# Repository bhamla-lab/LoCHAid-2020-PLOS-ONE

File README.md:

# LoCHAid
Repository for Addressing Age Related Hearing Loss through engineering accessible and affordable hearing technology
Data from ANSI Tests, Speechmap Tests, and KEMAR Tests are Present in the zip file Data ffor LoCHAid
.brd file for upload to OSHPARK is also present in HearinAid(2) .brd
The stl files for the boxed design are labeled by NEW {}. The bottom case is denoted by different degrees of taper - if there is wanting of a very tight fit of the top and bottom cases - use 3.5 degree taper file (NEW 3.5 deg bottom.stl). For semi-tight use the (NEW 3 deg bottom.stl). For just a bit of it use the (NEW 2.5 deg bottom.stl). We recommend the 3 degree taper.

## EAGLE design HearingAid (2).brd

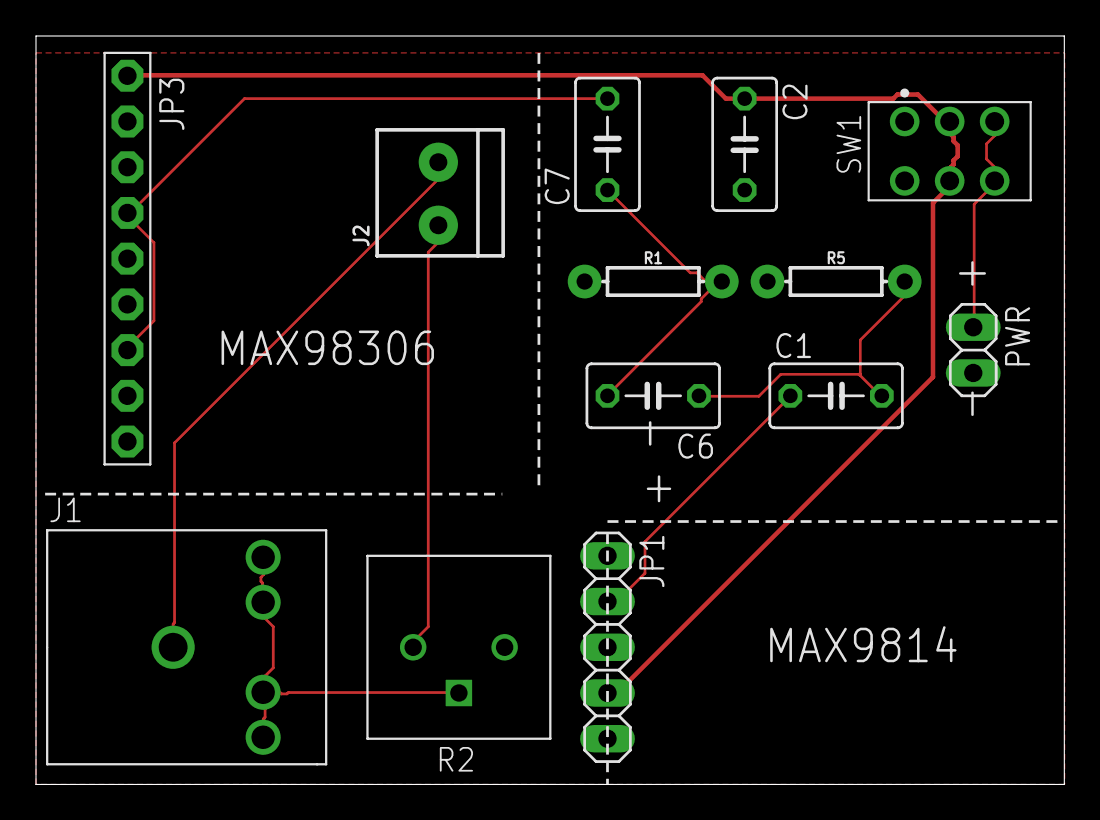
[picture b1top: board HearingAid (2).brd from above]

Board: 2 copper layers, 57.1 x 41.6 mm, 13 parts (0 on the bottom side), 10 nets.

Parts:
C1, C6: 1k pF; C050-035X075
C2: 1 uF; C050-035X075
C7: 16 uF; C050-035X075
J1: STX-3120-5B
J2: TERMBLOCK_1X2-3.5MM
JP1: 1X05
JP3: 1X09-BIG
PWR: 1X02
R1, R5: 6.8k; AXIAL-0.3
R2: 10K; 3-PRONG-TRIMPOT
SW1: JS202011CQN; HDRVR6W60P330X250_2X3_900X330X350B

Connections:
GND: C2.2, JP1.3, JP1.5, JP3.2, PWR.2, R1.P$1, R2.3, R5.P$1
unnamed: C1.2, C6.1, R5.P$2
unnamed: J1.2, J1.3, J1.4, J1.5, R2.2
unnamed: J2.2, R2.1
unnamed: J1.1, J2.1
unnamed: PWR.1, SW1.3, SW1.4
unnamed: C6.2, C7.1, R1.P$2
unnamed: C7.2, JP3.4, JP3.7
OUT: C1.1, JP1.2
VCC: C2.1, JP1.4, JP3.1, SW1.2, SW1.5

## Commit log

2020-09-24 Unaip all files so they can be browsed in GitHub
2021-12-28 Add files via upload
    Updated schematic to fix a typo on capacitor

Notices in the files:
parts and their libraries:
SparkFun-Resistors: Licensing: Creative Commons ShareAlike 4.0 International - https://creativecommons.org/licenses/by-sa/4.0
microbuilder: This work is placed in the public domain, and may be freely used for commercial and non-commercial work with the following conditions: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
